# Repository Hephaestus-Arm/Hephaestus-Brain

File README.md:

# Hephaestus-Brain
Samd 51 M4 based robot controller

# Breadboard and OTS variant

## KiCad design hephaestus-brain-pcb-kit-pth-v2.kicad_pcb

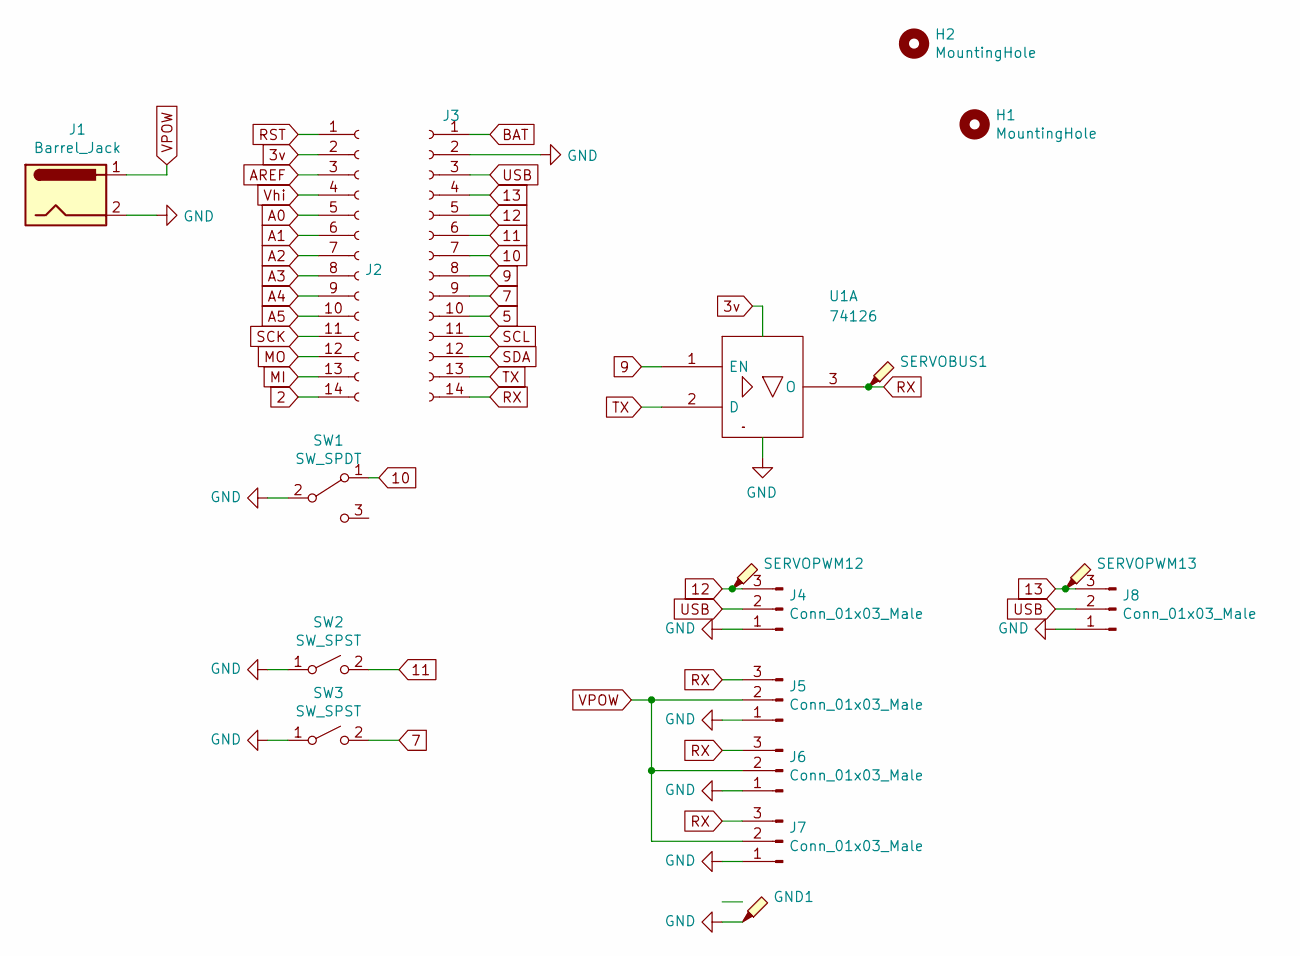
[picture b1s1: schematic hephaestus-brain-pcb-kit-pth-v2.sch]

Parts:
GND1: TestPoint_Probe; TestPoint_Keystone_5005-5009_Compact
H1, H2: MountingHole; MountingHole_2.2mm_M2
J1: Barrel_Jack; BarrelJack_CUI_PJ-102AH_Horizontal
J2, J3: ItsyBitsy; PinSocket_1x14_P2.54mm_Vertical
J4, J8: Conn_01x03_Male; PinSocket_1x03_P2.54mm_Vertical
J5, J6, J7: Conn_01x03_Male; JST_PH_B3B-PH-K_1x03_P2.00mm_Vertical
SERVOBUS1: TestPoint_Probe; TestPoint_Keystone_5005-5009_Compact
SERVOPWM12, SERVOPWM13: TestPoint_Probe; TestPoint_Keystone_5005-5009_Compact
SW1: SW_SPDT; SW_Slide_1P2T_CK_OS102011MS2Q
SW2, SW3: SW_SPST; SW_PUSH_6mm
U1: 74126; DIP-14_W7.62mm

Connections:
2: J2.14
3v: J2.2, U1.14 (VCC)
5: J3.10
7: J3.9, SW3.2 (B)
9: J3.8, U1.1 (EN)
10: J3.7, SW1.1 (A)
11: J3.6, SW2.2 (B)
12: J3.5, J4.3, SERVOPWM12.1
13: J3.4, J8.3, SERVOPWM13.1
A0: J2.5
A1: J2.6
A2: J2.7
A3: J2.8
A4: J2.9
A5: J2.10
AREF: J2.3
BAT: J3.1
GND: GND1.1, J1.2, J3.2, J4.1, J5.1, J6.1, J7.1, J8.1, SW1.2 (B), SW2.1 (A), SW3.1 (A), U1.7 (GND)
MI: J2.13
MO: J2.12
RST: J2.1
RX: J3.14, J5.3, J6.3, J7.3, SERVOBUS1.1, U1.3 (O)
SCK: J2.11
SCL: J3.11
SDA: J3.12
TX: J3.13, U1.2 (D)
USB: J3.3, J4.2, J8.2
VPOW: J1.1, J5.2, J6.2, J7.2
Vhi: J2.4

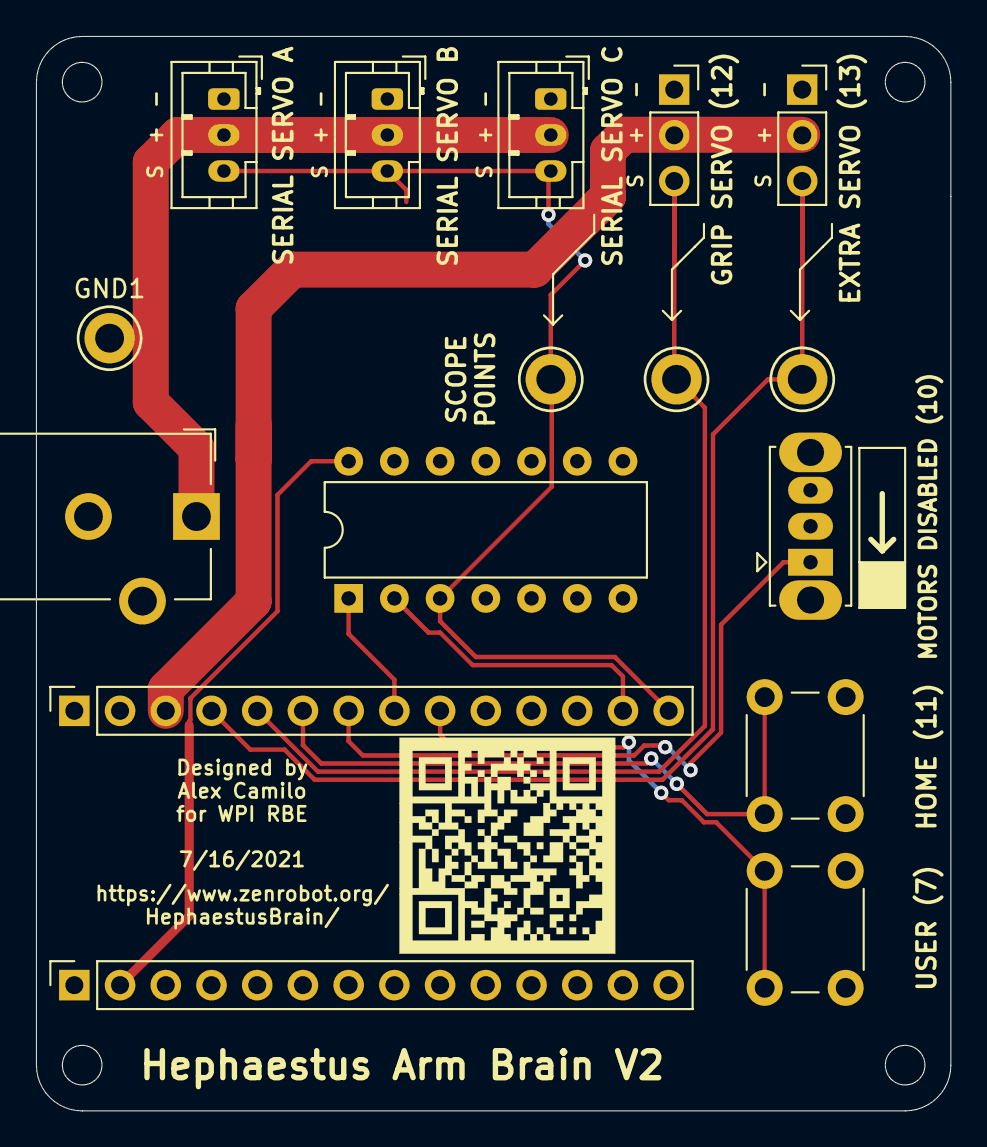
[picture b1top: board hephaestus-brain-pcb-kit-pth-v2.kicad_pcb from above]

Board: 2 copper layers, 50.8 x 59.7 mm, 21 parts (0 on the bottom side), 12 nets.

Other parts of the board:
H1#2, H1#3: MountingHole; MountingHole_2.2mm_M2
Ref**: Val**; QRCode

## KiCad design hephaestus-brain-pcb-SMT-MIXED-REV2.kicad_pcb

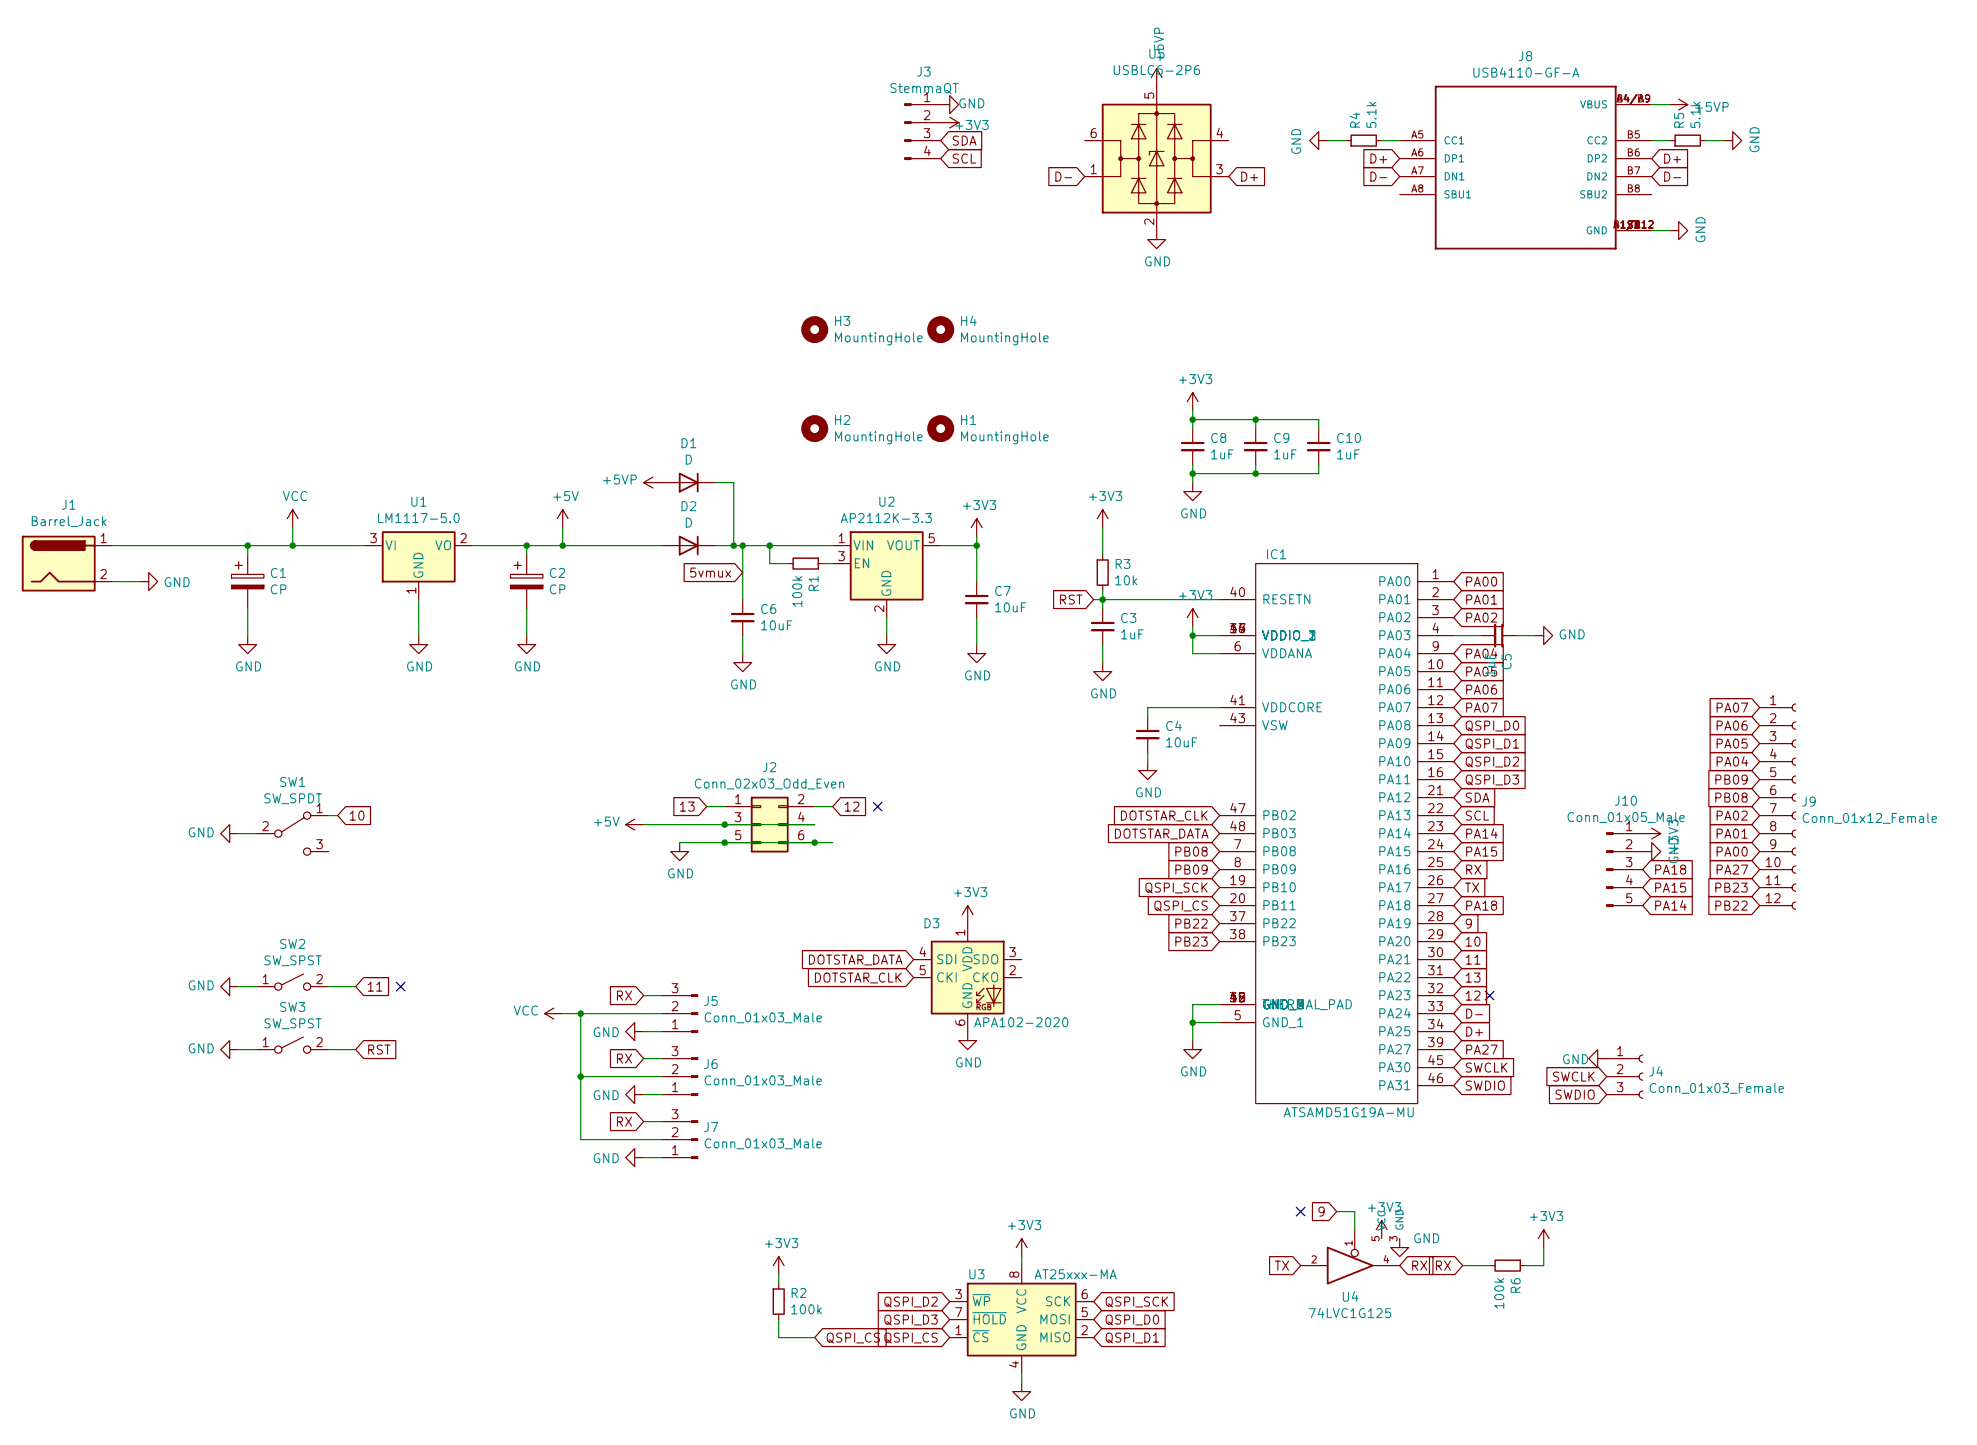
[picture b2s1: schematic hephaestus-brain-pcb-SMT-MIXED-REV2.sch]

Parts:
C1, C2: CP; C_0805_2012Metric
C3, C5, C8, C9, C10: 1uF; R_0603_1608Metric
C4, C6, C7: 10uF; R_0603_1608Metric
D1, D2: D; D_SOD-323
D3: APA102-2020; LED-APA102-2020
H1, H2, H3, H4: MountingHole; MountingHole_2.2mm_M2
IC1: ATSAMD51G19A-MU; QFN50P700X700X90-49N-D; Manufacturer_Part_Number ATSAMD51G19A-MU; Mouser Part Number 556-ATSAMD51G19AMU
J1: Barrel_Jack; BarrelJack_Wuerth_6941xx301002; mpn DC-005-5A-2.0-SMT; lcsc C319134
J2: Conn_02x03_Odd_Even; PinSocket_2x03_P2.54mm_Vertical
J3: StemmaQT; JST_SH_SM04B-SRSS-TB_1x04-1MP_P1.00mm_Horizontal
J4: Conn_01x03_Female; PinSocket_1x03_P2.54mm_Vertical
J5, J6, J7: Conn_01x03_Male; JST_PH_B3B-PH-K_1x03_P2.00mm_Vertical
J8: USB4110-GF-A; GCT_USB4110-GF-A
J9: Conn_01x12_Female; PinSocket_1x12_P2.54mm_Vertical
J10: Conn_01x05_Male; PinSocket_1x05_P2.54mm_Vertical
R1, R2, R6: 100k; R_0603_1608Metric
R3: 10k; R_0603_1608Metric
R4, R5: 5.1k; R_0603_1608Metric
SW1: SW_SPDT; SS12D06L5
SW2, SW3: SW_SPST; SW_SPST_TL3305C
U1: LM1117-5.0; SOT-223
U2: AP2112K-3.3; SOT-23-5; mpn AP2112K-3.3TRG1; lcsc C51118
U3: AT25xxx-MA; DFN-8-1EP_3x2mm_P0.5mm_EP1.75x1.45mm
U4: 74LVC1G125; SOT-353_SC-70-5
U5: USBLC6-2P6; SOT-666

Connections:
5vmux: C6.1, D1.1 (K), D2.1 (K), R1.2, U2.1 (VIN)
9: IC1.28 (PA19), U4.1
10: IC1.29 (PA20), SW1.1 (A)
11: IC1.30 (PA21), SW2.2 (B)
12: IC1.32 (PA23), J2.2
13: IC1.31 (PA22), J2.1
+3V3: C7.1, C8.1, C9.1, C10.1, D3.1 (VDD), IC1.6 (VDDANA), IC1.17 (VDDIO_1), IC1.36 (VDDIO_2), IC1.44 (VDDIO_3), J3.2, J10.1, R2.1, R3.1, R6.1, U2.5 (VOUT), U3.8 (VCC), U4.5 (VCC)
+5V: C2.1, D2.2 (A), J2.3, J2.4, U1.2 (VO)
+5VP: D1.2 (A), J8.A4/B9 (VBUS), J8.B4/A9 (VBUS), U5.5 (VBUS)
D+: IC1.34 (PA25), J8.A6 (DP1), J8.B6 (DP2), U5.3 (I/O2)
D-: IC1.33 (PA24), J8.A7 (DN1), J8.B7 (DN2), U5.1 (I/O1)
DOTSTAR_CLK: D3.5 (CKI), IC1.47 (PB02)
DOTSTAR_DATA: D3.4 (SDI), IC1.48 (PB03)
GND: C1.2, C2.2, C3.2, C4.2, C5.1, C6.2, C7.2, C8.2, C9.2, C10.2, D3.6 (GND), IC1.5 (GND_1), IC1.18 (GND_2), IC1.35 (GND_3), IC1.42 (GND_4), IC1.49 (THERMAL_PAD), J1.2, J2.5, J2.6, J3.1, J4.1, J5.1, J6.1, J7.1, J8.A1/B12 (GND), J8.B1/A12 (GND), J8.S1 (GND), J8.S2 (GND), J8.S3 (GND), J8.S4 (GND), J10.2, R4.1, R5.2, SW1.2 (B), SW2.1 (A), SW3.1 (A), U1.1 (GND), U2.2 (GND), U3.4 (GND), U3.9 (GND), U4.3 (GND), U5.2 (GND)
unnamed: C4.1, IC1.41 (VDDCORE)
unnamed: C5.2, IC1.4 (PA03)
unnamed: J8.A5 (CC1), R4.2
unnamed: J8.B5 (CC2), R5.1
unnamed: R1.1, U2.3 (EN)
PA00: IC1.1 (PA00), J9.9
PA01: IC1.2 (PA01), J9.8
PA02: IC1.3 (PA02), J9.7
PA04: IC1.9 (PA04), J9.4
PA05: IC1.10 (PA05), J9.3
PA06: IC1.11 (PA06), J9.2
PA07: IC1.12 (PA07), J9.1
PA14: IC1.23 (PA14), J10.5
PA15: IC1.24 (PA15), J10.4
PA18: IC1.27 (PA18), J10.3
PA27: IC1.39 (PA27), J9.10
PB08: IC1.7 (PB08), J9.6
PB09: IC1.8 (PB09), J9.5
PB22: IC1.37 (PB22), J9.12
PB23: IC1.38 (PB23), J9.11
QSPI_CS: IC1.20 (PB11), R2.2, U3.1 (~CS)
QSPI_D0: IC1.13 (PA08), U3.5 (MOSI)
QSPI_D1: IC1.14 (PA09), U3.2 (MISO)
QSPI_D2: IC1.15 (PA10), U3.3 (~WP)
QSPI_D3: IC1.16 (PA11), U3.7 (~HOLD)
QSPI_SCK: IC1.19 (PB10), U3.6 (SCK)
RST: C3.1, IC1.40 (RESETN), R3.2, SW3.2 (B)
RX: IC1.25 (PA16), J5.3, J6.3, J7.3, R6.2, U4.4
SCL: IC1.22 (PA13), J3.4
SDA: IC1.21 (PA12), J3.3
SWCLK: IC1.45 (PA30), J4.2
SWDIO: IC1.46 (PA31), J4.3
TX: IC1.26 (PA17), U4.2
VCC: C1.1, J1.1, J5.2, J6.2, J7.2, U1.3 (VI)

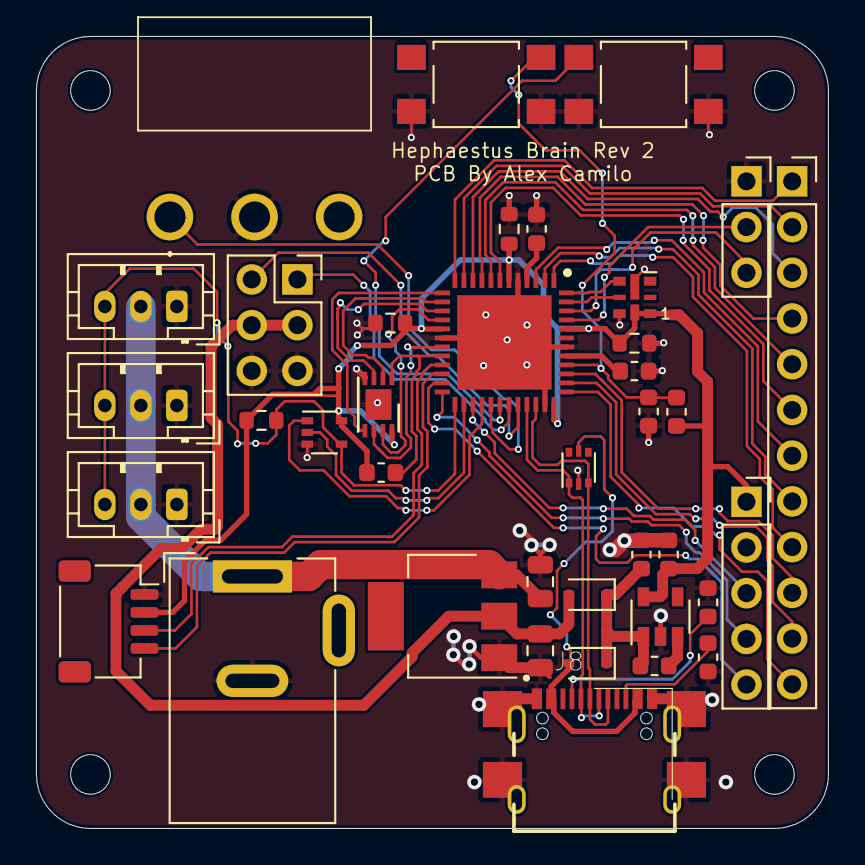
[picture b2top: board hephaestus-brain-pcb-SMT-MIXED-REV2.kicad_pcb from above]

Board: 2 copper layers, 44.0 x 44.0 mm, 42 parts (0 on the bottom side), 48 nets.

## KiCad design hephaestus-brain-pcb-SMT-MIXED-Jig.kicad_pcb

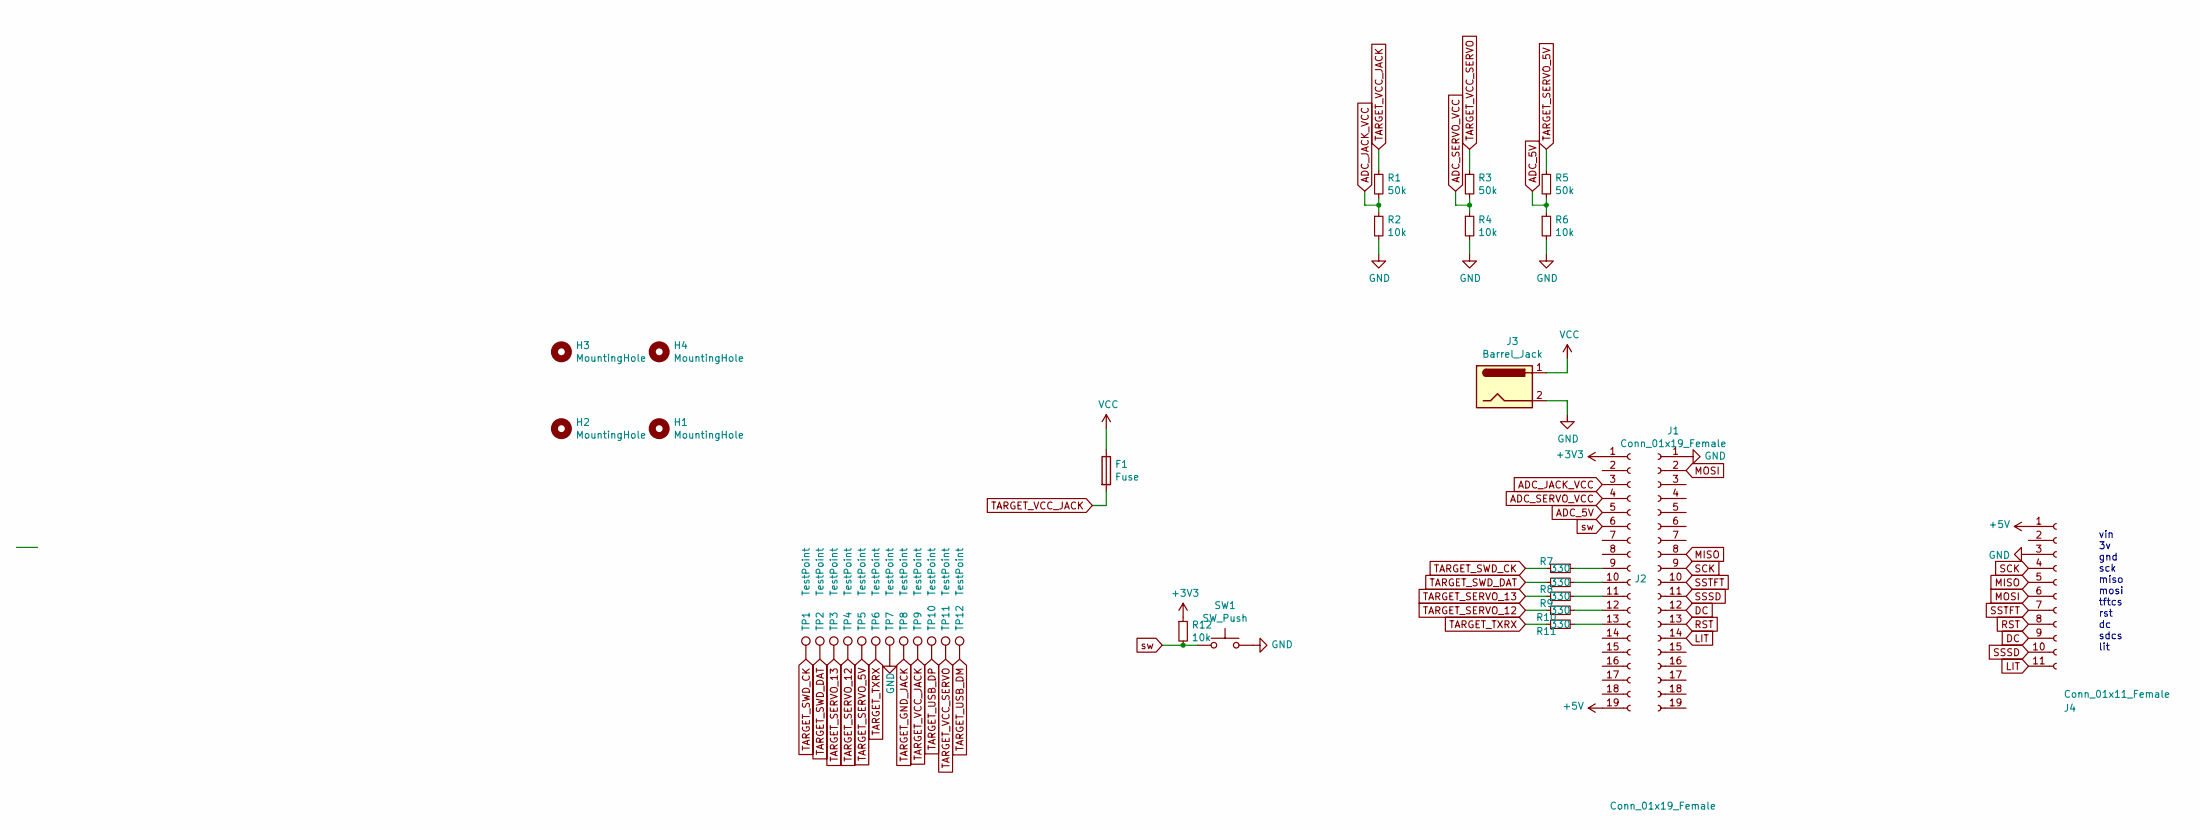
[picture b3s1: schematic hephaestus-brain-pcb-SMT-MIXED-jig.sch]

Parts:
F1: Fuse; NANO-0154-OMNI-BLOK-Fuse-Holder
H1, H2, H3, H4: MountingHole; MountingHole_2.2mm_M2
J1, J2: Conn_01x19_Female; PinSocket_1x19_P2.54mm_Vertical
J3: Barrel_Jack; BarrelJack_Wuerth_6941xx301002
J4: Conn_01x11_Female; PinSocket_1x11_P2.54mm_Vertical
R1, R3, R5: 50k; R_0603_1608Metric
R2, R4, R6, R12: 10k; R_0603_1608Metric
R7, R8, R9, R10, R11: 330; R_0603_1608Metric
SW1: SW_Push; SW_PUSH_6mm
TP1, TP2, TP3, TP4, TP5, TP6, TP7, TP8, TP9, TP10, TP11, TP12: TestPoint; TestPoint_Pad_D1.5mm

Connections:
+3V3: J2.1, R12.1
+5V: J2.19, J4.1
ADC_5V: J2.5, R5.2, R6.1
ADC_JACK_VCC: J2.3, R1.2, R2.1
ADC_SERVO_VCC: J2.4, R3.2, R4.1
DC: J1.12, J4.9
GND: J1.1, J3.2, J4.3, R2.2, R4.2, R6.2, SW1.2, TP7.1
LIT: J1.14, J4.11
MISO: J1.8, J4.5
MOSI: J1.2, J4.6
unnamed: J2.9, R7.1
unnamed: J2.10, R8.2
unnamed: J2.11, R9.2
unnamed: J2.12, R10.2
unnamed: J2.13, R11.2
RST: J1.13, J4.8
SCK: J1.9, J4.4
SSSD: J1.11, J4.10
SSTFT: J1.10, J4.7
TARGET_GND_JACK: TP8.1
TARGET_SERVO_5V: R5.1, TP5.1
TARGET_SERVO_12: R10.1, TP4.1
TARGET_SERVO_13: R9.1, TP3.1
TARGET_SWD_CK: R7.2, TP1.1
TARGET_SWD_DAT: R8.1, TP2.1
TARGET_TXRX: R11.1, TP6.1
TARGET_USB_DM: TP12.1
TARGET_USB_DP: TP10.1
TARGET_VCC_JACK: F1.2, R1.1, TP9.1
TARGET_VCC_SERVO: R3.1, TP11.1
VCC: F1.1, J3.1
sw: J2.6, R12.2, SW1.1

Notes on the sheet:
vin 3v gnd sck miso mosi tftcs rst dc sdcs lit

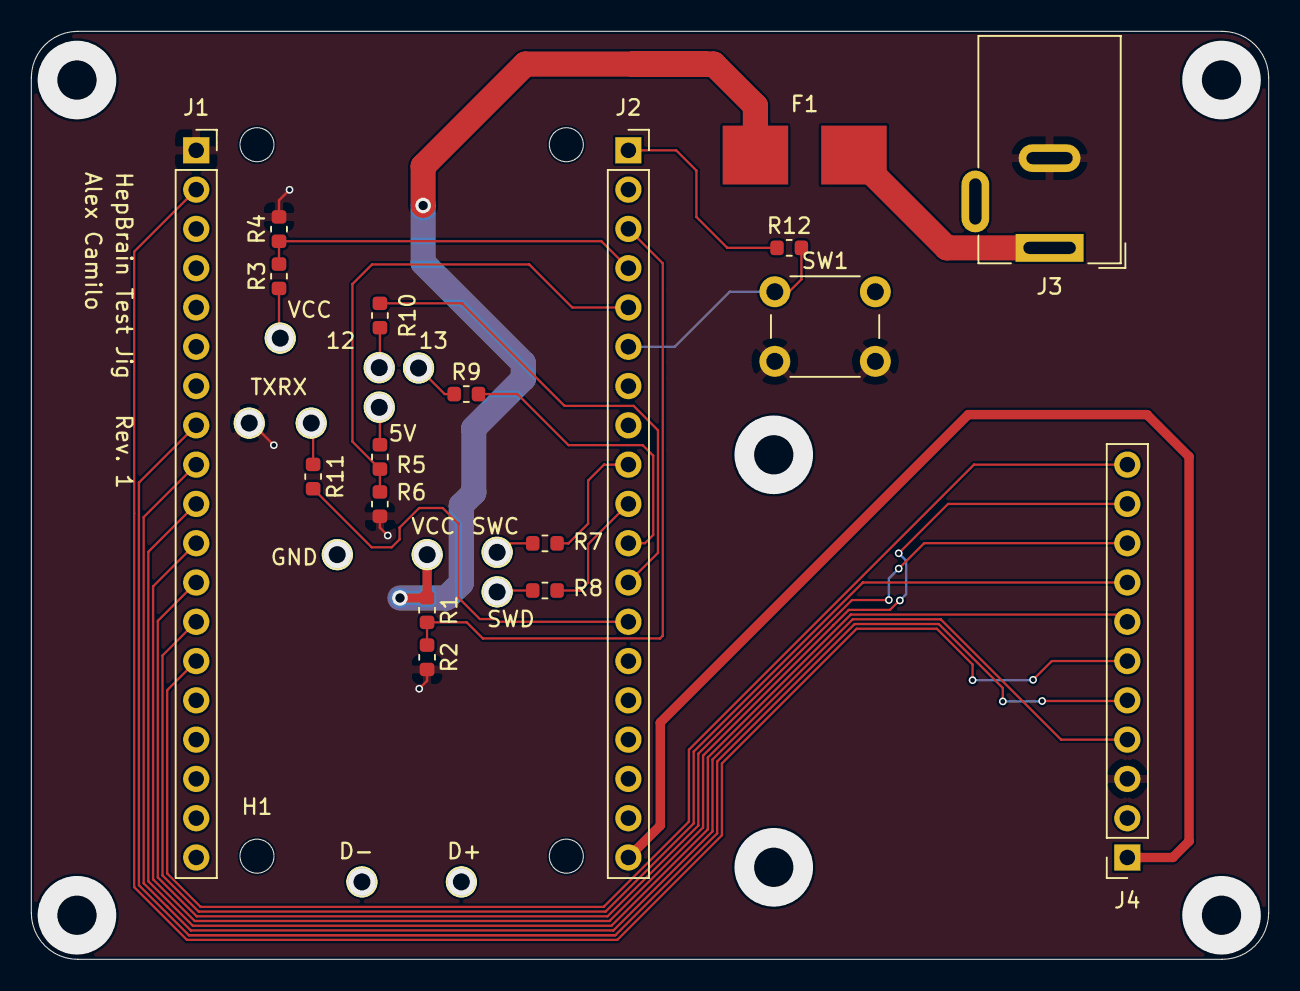
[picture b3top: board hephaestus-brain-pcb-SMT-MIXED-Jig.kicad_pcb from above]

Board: 2 copper layers, 80.0 x 60.0 mm, 34 parts (0 on the bottom side), 29 nets.

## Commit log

2020-07-22 Rev 1 of board done.
2020-07-22 Added homing switch connector
2020-07-23 Added switch, button.
2020-07-23 Updated Silkscreen
2020-08-12 Add board render and wiring diagram
2020-08-12 layer vis, minor visual edits.
2020-08-12 png version
2020-10-29 Added bom. FP fix.
2020-10-29 updated bom to add missing PN
2020-10-29 uncomitted pcb edits
2020-11-09 SMT Version of brain
2020-11-09 layout done
2020-11-11 Revision 1 of SMT version
2020-11-12 Mixed SMT-PTH version.
2020-11-12 routing tweaks
2020-11-13 Switched over to USBC connector.
2020-11-13 Added SWD Connector and QWIIC
2020-11-13 Added more robust USBC Connector
2020-11-13 Swapped out barrel jack footprint.
2020-11-13 Fixed soldermask issue.
2020-11-13 Added BOM
2020-11-13 Added board Artwork
2020-11-13 Switched one of the extra buttons to RESET
2020-11-13 placment info
2020-11-14 Changed with of soldermask between pads to meet MFG spec.
    Changed from 0.2mm to 0.23mm. spec is 0.22mm for red soldermask.
2020-11-17 Updated footprints.
    0.22mm soldermask clearence on the USB and flash ICs
2020-11-19 Testing Jig
2020-11-20 finished jig pcb
2020-11-20 updated footprints
2021-03-18 Revision 2
2021-06-16 Rev2 of the kit version of the board
    * Spaced everything out, updated silkscreen.
    * moved usb and power to the same edge of the board
    * Switched button IO from 9 to 7
2021-07-16 Updated silkscreen
    * added QR code
    * added board name, rev, author.
